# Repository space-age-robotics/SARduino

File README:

See http://www.spaceagerobotics.com/blog/projects/sarduino/ for more information.

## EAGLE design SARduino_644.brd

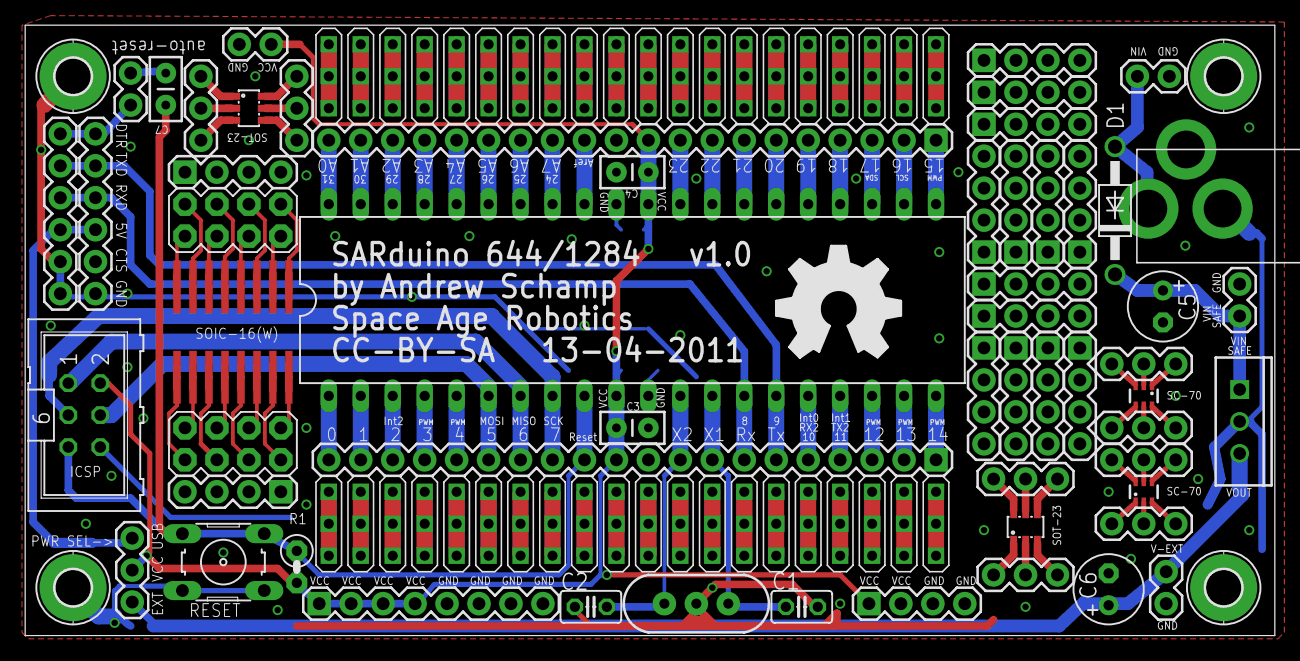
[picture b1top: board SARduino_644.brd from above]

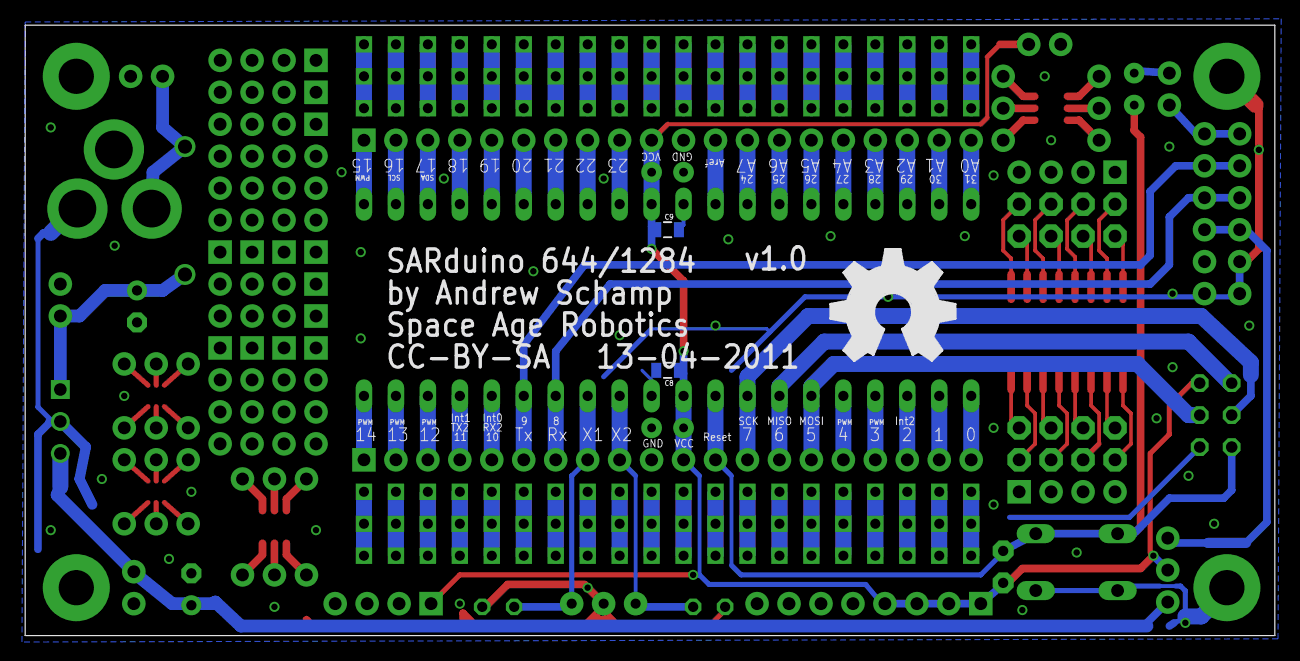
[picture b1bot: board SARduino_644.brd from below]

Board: 2 copper layers, 99.3 x 48.5 mm, 106 parts (3 on the bottom side), 84 nets.

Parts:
C1, C2: 22pf; C025-025X050
C3, C4, C7: 0.1uF; CAP-PTH-SMALL2
C5, C6: 100uF; E2,5-6
C8, C9: 0.1uF; 0805
D1: 1N4001; DO41-10
IC1: ATMEGA644P; DIL40
JP1, JP2, JP5, JP6, JP8, JP11, JP12, JP13, JP24: 1X03
JP3, JP4, JP7, JP9: MOUNT-PAD-ROUND2.8; 2,8-PAD
JP10, JP25: FTDI_BASICPTH; FTDI_BASIC_NO_LABEL
JP14, JP15, JP16, JP17, JP18, JP19, JP20, JP21, JP22, JP23, JP26, JP27, JP35, JP37, JP38, JP39: 1X04
JP28, JP31, JP32, JP33, JP36: 1X02
JP29, JP30: M20; 1X20
JP34: 1X08
LOGO1, LOGO2: OSHW_LOGO_FILLX0350-NT; OSHW_FILLX350_NOTEXT
R1: 10k; 0207/2V
S1: B3F-10XX
SV1: ML6
U$1: 2.1MMJACKTHM; PJ-102A
U$2, U$9, U$10, U$11, U$12, U$13, U$14, U$15, U$16, U$17, U$18, U$19, U$20, U$21, U$22, U$23, U$24, U$25, U$26, U$27, U$28, U$29, U$30, U$31, U$32, U$33, U$34, U$35, U$36, U$37, U$38, U$39, U$40, U$41, U$42, U$43, U$44, U$45, U$46, U$47: 3-PIN-STRIP; 1X03_STRIP
U$3: 16-PINSOICW; SO16W
U$4: 16-PINSOIC; SO16
U$5, U$6: M04X2; 2X4
U$8, U$50: 6-PINSC70-6; SC70-6L
U$48, U$53: 6-PINSOT23-6; SOT23-6L
VR-TOP: 7805; TO220-IGO
Y1: RESONATOR; RESONATOR/CRYSTAL_COMBO

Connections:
644P1: IC1.1, JP30.20
644P2: IC1.2, JP30.19
644P3: IC1.3, JP30.18
644P4: IC1.4, JP30.17
644P5: IC1.5, JP30.16
644P16: IC1.16, JP30.5
644P17: IC1.17, JP30.4
644P18: IC1.18, JP30.3
644P19: IC1.19, JP30.2
644P20: IC1.20, JP30.1
644P21: IC1.21, JP29.1
644P22: IC1.22, JP29.2
644P23: IC1.23, JP29.3
644P24: IC1.24, JP29.4
644P25: IC1.25, JP29.5
644P26: IC1.26, JP29.6
644P27: IC1.27, JP29.7
644P28: IC1.28, JP29.8
644P29: IC1.29, JP29.9
644P33: IC1.33, JP29.13
644P34: IC1.34, JP29.14
644P35: IC1.35, JP29.15
644P36: IC1.36, JP29.16
644P37: IC1.37, JP29.17
644P38: IC1.38, JP29.18
644P39: IC1.39, JP29.19
644P40: IC1.40, JP29.20
AREF: IC1.32, JP29.12
DTR: JP10.DTR, JP25.DTR, JP28.1
GND: C1.1, C2.1, C3.2, C4.2, C5.-, C6.-, C8.2, C9.2, IC1.11, IC1.31, JP3.B2,8, JP4.B2,8, JP7.B2,8, JP9.B2,8, JP10.CTS, JP10.GND, JP25.CTS, JP25.GND, JP29.11, JP30.10, JP31.1, JP32.1, JP33.2, JP34.5, JP34.6, JP34.7, JP34.8, JP35.3, JP35.4, JP36.2, S1.3, S1.4, SV1.6, U$1.RING, VR-TOP.GND, Y1.2
MISO: IC1.7, JP30.14, SV1.1
MOSI: IC1.6, JP30.15, SV1.4
unnamed: JP1.3, U$8.4
unnamed: JP1.2, U$8.5
unnamed: JP1.1, U$8.6
unnamed: JP2.3, U$48.4
unnamed: JP2.2, U$48.5
unnamed: JP2.1, U$48.6
unnamed: JP5.1, U$48.3
unnamed: JP5.2, U$48.2
unnamed: JP5.3, U$48.1
unnamed: JP8.1, U$8.3
unnamed: U$3.16, U$4.16, U$5.1
unnamed: U$3.15, U$4.15, U$5.2
unnamed: JP8.2, U$8.2
unnamed: U$3.5, U$4.5, U$6.5
unnamed: U$3.1, U$4.1, U$6.1
unnamed: JP8.3, U$8.1
unnamed: JP11.3, U$50.4
unnamed: JP11.2, U$50.5
unnamed: JP11.1, U$50.6
unnamed: JP12.1, U$50.3
unnamed: U$3.14, U$4.14, U$5.3
unnamed: U$3.13, U$4.13, U$5.4
unnamed: U$3.12, U$4.12, U$5.5
unnamed: U$3.11, U$4.11, U$5.6
unnamed: U$3.10, U$4.10, U$5.7
unnamed: U$3.9, U$4.9, U$5.8
unnamed: U$3.8, U$4.8, U$6.8
unnamed: U$3.7, U$4.7, U$6.7
unnamed: U$3.6, U$4.6, U$6.6
unnamed: JP12.2, U$50.2
unnamed: U$3.4, U$4.4, U$6.4
unnamed: U$3.2, U$4.2, U$6.2
unnamed: JP12.3, U$50.1
unnamed: JP13.3, U$53.4
unnamed: JP13.2, U$53.5
unnamed: JP13.1, U$53.6
unnamed: JP24.1, U$53.3
unnamed: JP24.2, U$53.2
unnamed: JP24.3, U$53.1
unnamed: C7.1, JP28.2
unnamed: U$3.3, U$4.3, U$6.3
RESET: C7.2, IC1.9, JP30.12, R1.1, S1.1, S1.2, SV1.5
RXD: IC1.14, JP10.TXO, JP25.TXO, JP30.7
SCK: IC1.8, JP30.13, SV1.3
TXD: IC1.15, JP10.RXI, JP25.RXI, JP30.6
USB_5V: JP6.1, JP10.VCC, JP25.VCC
VCC: C3.1, C4.1, C8.1, C9.1, IC1.10, IC1.30, JP6.2, JP29.10, JP30.11, JP34.1, JP34.2, JP34.3, JP34.4, JP35.1, JP35.2, JP36.1, R1.2, SV1.2
VIN: D1.A, JP32.2, U$1.TIP
VIN_SAFE: C5.+, D1.C, JP31.2, VR-TOP.IN
VREG-OUT: C6.+, JP6.3, JP33.1, VR-TOP.OUT
XTAL1: C1.2, IC1.13, JP30.8, Y1.3
XTAL2: C2.2, IC1.12, JP30.9, Y1.1

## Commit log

2012-01-21 updated for 0.1 release
2012-01-21 Added first README file
2012-01-21 added PNGs of boards and schematics
2012-04-14 First round of updates
    Clean up and separate proto areas, rearrange power supply,
    address some open issues:
    Closes #4
    Closes #6
    Closes #7
    Closes #8
2012-04-15 Fix reference designators
    Remove extraneous designators from proto areas, make sure all other
    designators are reasonable.
    Closes #1
2012-04-15 Added some more proto area
    Also add value lables to most passives.
    Closes #2
    Closes #3
2012-05-13 Update for 644 v1.0, add images, gerbers, panel gerbers, panel config
2012-05-13 fix name of panel .zip
2012-09-03 Updated gerbers to not include Seeed Order Number
    Updated panel.cfg for smaller cutlines
